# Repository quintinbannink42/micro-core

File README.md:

# Micro Core

Core EFI Hellen-One rusEFI ECU. Microsquirt-class sealed box, 35-way AMPSEAL, **vertical header**.

4-cylinder sequential wire-in. **STM32F407VGT6** on Hellen `mega-mcu100/0.3` (not mega-mcu64). Seven NCE4080K power FETs: 4 injector channels (2× high-Z each) plus fuel-pump, idle, and boost low-sides with US1M flyback and SMAJ33A. Gates are driven from `/V12_RAW` by SLM27524CA-DG low-side drivers, not directly from the 3.3 V GPIO.

## Status

Spec locked in [docs/SPEC.md](docs/SPEC.md). Hardware on this branch: **rev q**. Q1–Q7 are NCE4080K (LCSC C191380) on the existing DPAK land. Four SLM27524CA-DG drivers (LCSC C2921387) take the mega-mcu100 GPIO and drive the gates from `/V12_RAW` through the 12 ohm series resistors. Seven of eight channels are used; the spare input is tied to GND. Q5–Q7 (AMPSEAL pins 8/9/10, FP / Idle / Boost) keep the US1M flyback and SMAJ33A from rev p. F407VGT6 on mega-mcu100 stays. `boards/microcore-q/` lands when Create Board succeeds on `main` after merge. See [docs/HARDWARE_STATUS_rev_q.md](docs/HARDWARE_STATUS_rev_q.md). **Not production-ready.** The earlier FET comparison is in [docs/FET_COMPARISON.md](docs/FET_COMPARISON.md).

- Header: TE **776231-1** (straight / vertical)
- Plug: TE **776164-1** black, key A
- Not 776163-1 (right-angle)
- USB: vertical Mini-B on the frame (`hellen-one-common:USB_B_Mini` / `USB-MINI-B-VERTICAL`), gasketed flap or pigtail — not on the 35-way AMPSEAL

## Spec

See [docs/SPEC.md](docs/SPEC.md). Boss brief: [MICROCORE_BRIEF.md](MICROCORE_BRIEF.md).

Hellen tips: [docs/HELLEN-FAQ.md](docs/HELLEN-FAQ.md).

Firmware board name: `coreefi_micro` (sibling tree `/workspace/fw-coreefi-micro`, not in this repo). The MCU is the F407 from rev n; that firmware tree will need an F407 target later. This repo does not publish a firmware remote.

KiCad board basename: `microcore` (`BOARD_PREFIX=micro`, `BOARD_SUFFIX=core`, rev `q`).

## Hellen tooling

- Submodules: `hellen-one` (andreika-git/hellen-one), `kicad6-libraries` (rusefi/kicad6-libraries)
- CI: Create Board on push to `main`; daily submodule update workflows
- Fab outputs on main include `boards/microcore-p/`. After merge, Create Board writes `boards/microcore-q/`
- Local DRC needs **KiCad 10** (`kicad-cli`); board file is generator_version 10.0
- Empty-PCB guard: `bin/check-pcb-not-empty.sh` (Create Board job `guard-pcb-not-empty`)

## License

Hardware and docs in this repo: use for Core EFI product development.
Firmware will track rusEFI (GPL) when the board config lands.

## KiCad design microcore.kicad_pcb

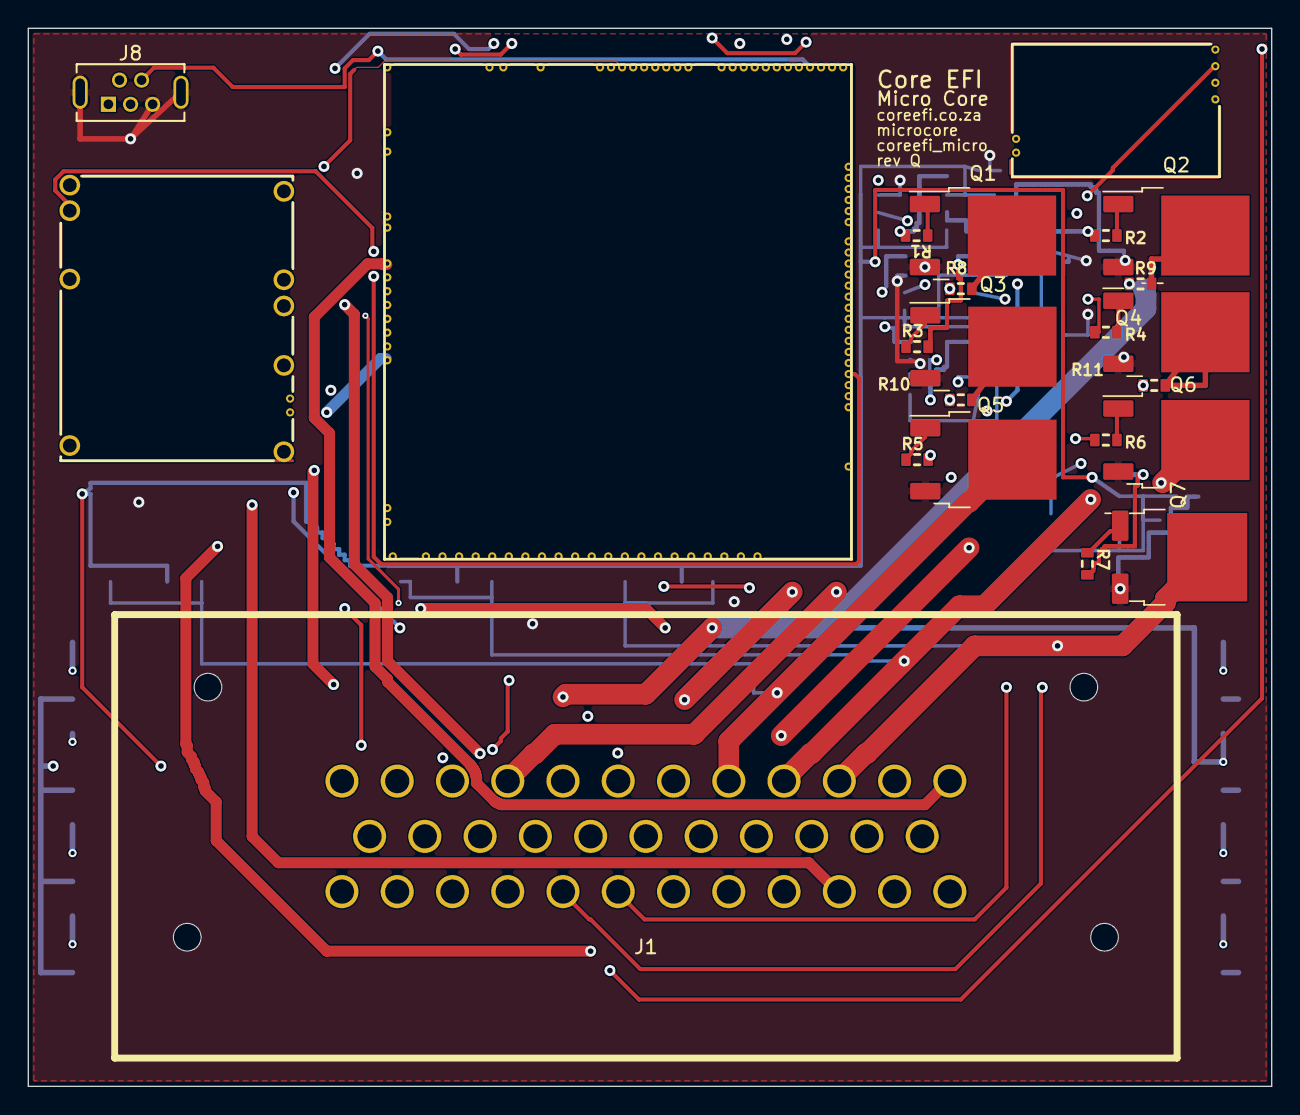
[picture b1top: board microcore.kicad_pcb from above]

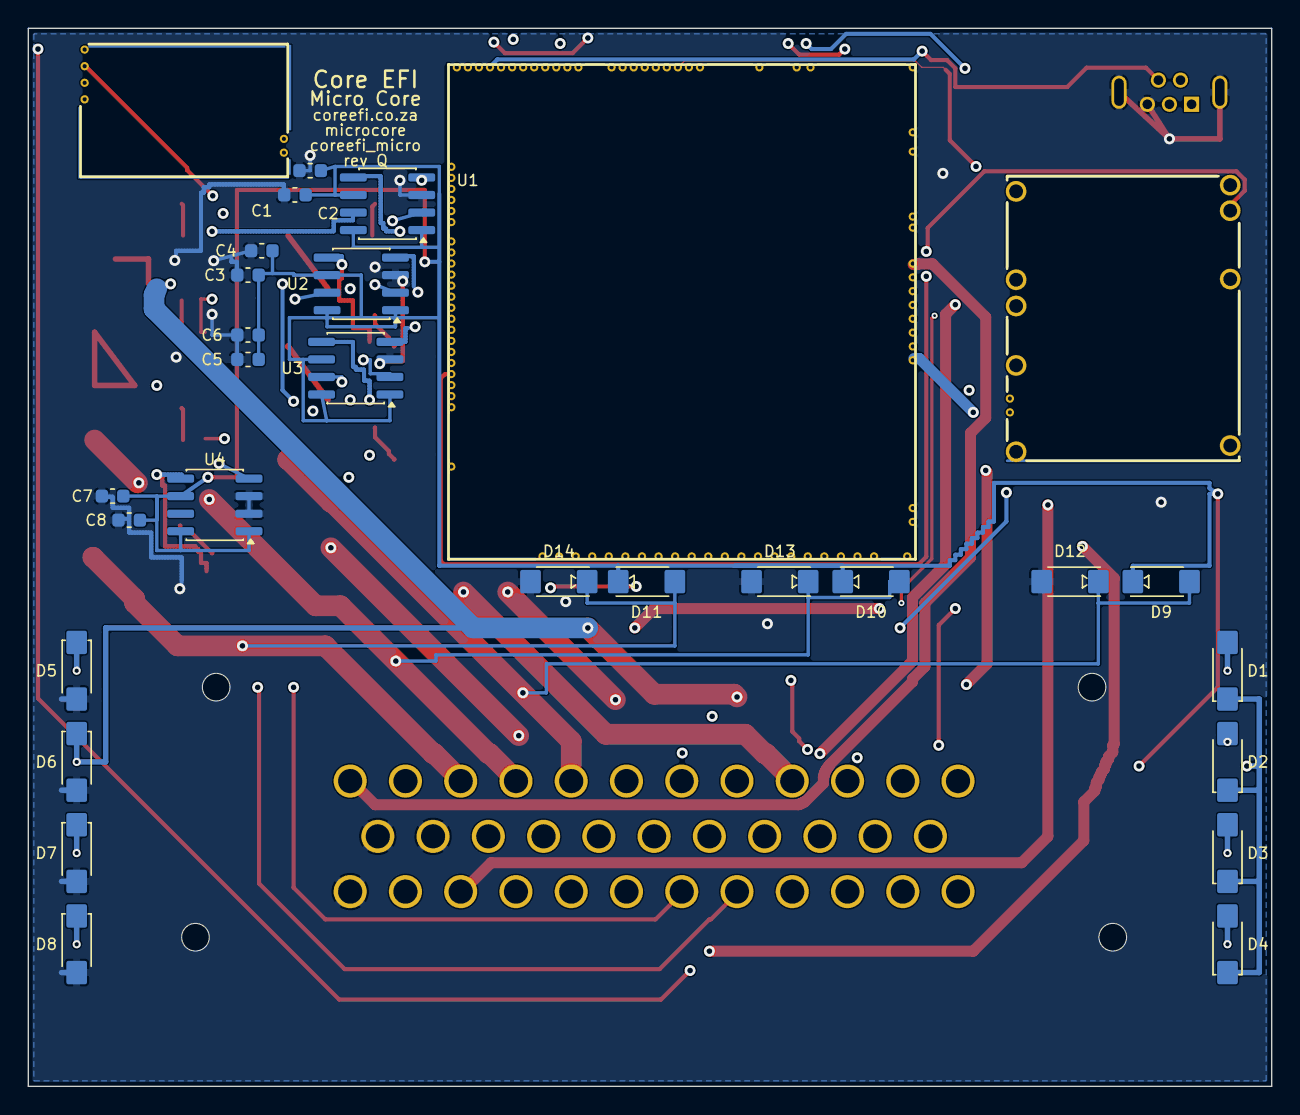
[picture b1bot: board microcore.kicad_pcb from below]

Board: 4 copper layers, 90.0 x 76.6 mm, 49 parts (26 on the bottom side), 64 nets.

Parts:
C1, C3, C5, C7: 100n; C0603
C2, C4, C6, C8: 1u; C0603
D1, D2, D3, D4, D9, D10, D11: US1M; DO214AC
D5, D6, D7, D8, D12, D13, D14: SMAJ33A; DO214AC
J1: TE_776231-1; TE_776231
J8: USB_B_Mini; USB-MINI-B-VERTICAL
M1: Module:mega-mcu100/0.3; mega-mcu100
M2: Module-power_12and5V-0.3; power_12and5V
M3: Module-vr-max9924-0.3; vr-max9924
Q1, Q2, Q3, Q4, Q5, Q6, Q7: NCE4080K; DPAK
R1, R2, R3, R4, R5, R6, R7, R8, R9, R10, R11: 12; R0603
U1, U2, U3, U4: SLM27524CA-DG; SOIC-8

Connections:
/AN1: J1.19, M1.S9 (IN_AUX1_(PB0))
/AN2: J1.21, M1.S8 (IN_AUX2_(PC4/PE9))
/CAN_H: J1.2, M1.W11 (CANH)
/CAN_L: J1.3, M1.W12 (CANL)
/CLT: J1.24, M1.S21 (IN_CLT_(PC2))
/DIN1: J1.11, M1.S4 (IN_D1_(PE12))
/DIN2: J1.26, M1.S3 (IN_D2_(PE13))
/HALL_CAM: J1.27, M1.S16 (IN_CAM_(PA6))
/IAT: J1.25, M1.S20 (IN_IAT_(PC3))
/IGN1: J1.12, M1.W10 (IGN1_(PC13))
/IGN2: J1.13, M1.W9 (IGN2_(PE5))
/IGN3: J1.14, M1.W8 (IGN3_(PE4))
/IGN4: J1.15, M1.W7 (IGN4_(PE3))
/IGN5: J1.30, M1.W6 (IGN5_(PE2))
/IGN6: J1.31, M1.W5 (IGN6_(PB8))
/IGN7: J1.32, M1.W4 (IGN7_(PB9))
/IGN8: J1.33, M1.W3 (IGN8_(PE6))
/INJ1: D1.2, D5.1, J1.4, R8.1
/INJ2: D2.2, D6.1, J1.5, R9.1
/INJ3: D3.2, D7.1, J1.6, R10.1
/INJ4: D4.2, D8.1, J1.7, R11.1
/LS1_FP: D9.2, D12.1, J1.8, Q5.2
/LS2_IDLE: D10.2, D13.1, J1.9, Q6.2
/LS3_BOOST: D11.2, D14.1, J1.10, Q7.2
/MAP: J1.18, M1.S13 (IN_MAP1_(PC0))
/OUT_INJ1: M1.E17 (OUT_INJ1_(PD3)), U1.4
/OUT_INJ2: M1.E16 (OUT_INJ2_(PA9)), U1.2
/OUT_INJ3: M1.E15 (OUT_INJ3_(PD11)), U2.4
/OUT_INJ4: M1.E14 (OUT_INJ4_(PD10)), U2.2
/OUT_LS1: M1.E18 (OUT_PWM1_(PD13)), U3.4
/OUT_LS2: M1.E19 (OUT_PWM2_(PC6)), U3.2
/OUT_LS3: M1.E20 (OUT_PWM3_(PC7)), U4.4
/SGND: J1.20, J1.34, M1.E2 (GNDA), M1.W1 (GNDA)
/TPS: J1.17, M1.S18 (IN_TPS_(PA4))
/USBID_(PA10): J8.4, M1.N4 (USBID_(PA10))
/USBM_(PA11): J8.2, M1.N2 (USBM_(PA11))
/USBP_(PA12): J8.3, M1.N3 (USBP_(PA12))
/V5_REF: J1.16, M2.E4 (V5), M3.E4 (V5_IN)
/V12_RAW: C1.2, C2.2, C3.2, C4.2, C5.2, C6.2, C7.2, C8.2, D1.1, D2.1, D3.1, D4.1, D9.1, D10.1, D11.1, J1.1, M2.V3 (V12_RAW), U1.1, U1.6, U1.8, U2.1, U2.6, U2.8, U3.1, U3.6, U3.8, U4.1, U4.6, U4.8
/VBAT: M1.N17 (VBAT), M2.E1 (VBAT)
/VBUS: J8.1, M1.N1 (VBUS)
/VIGN_SENSE: M1.E5 (IN_VIGN_(PA5)), M2.V2 (IN_VIGN)
/VR_N: J1.29, M3.W1 (VR-)
/VR_OUT: M1.S14 (IN_CRANK_(PB1)), M3.E3 (OUT)
/VR_P: J1.28, M3.W2 (VR+)
GND: C1.1, C2.1, C3.1, C4.1, C5.1, C6.1, C7.1, C8.1, D5.2, D6.2, D7.2, D8.2, D12.2, D13.2, D14.2, J1.22, J1.23, J1.35, J8.5, J8.6, M1.G (GND), M2.S1 (GND), M3.G (GND), Q1.3, Q2.3, Q3.3, Q4.3, Q5.3, Q6.3, Q7.3, U1.3, U2.3, U3.3, U4.2, U4.3
unnamed: Q1.2, R8.2
unnamed: Q1.1, R1.1
unnamed: Q2.2, R9.2
unnamed: Q2.1, R2.1
unnamed: Q3.2, R10.2
unnamed: Q3.1, R3.1
unnamed: Q4.2, R11.2
unnamed: Q4.1, R4.1
unnamed: Q5.1, R5.1
unnamed: Q6.1, R6.1
unnamed: Q7.1, R7.1
unnamed: R2.2, U1.7
unnamed: R1.2, U1.5
unnamed: R4.2, U2.7
unnamed: R3.2, U2.5
unnamed: R6.2, U3.7
unnamed: R5.2, U3.5
unnamed: R7.2, U4.5
